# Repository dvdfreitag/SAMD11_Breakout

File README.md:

# SAMD11_Breakout
A breakout board for the Atmel ATSAMD11 microcontroller in QFN24

The ATSAMD11 is an extremely inexpensive USB-enabled microcontroller with an Arm Cortex-M0+ core running at a maximum 48MHz.

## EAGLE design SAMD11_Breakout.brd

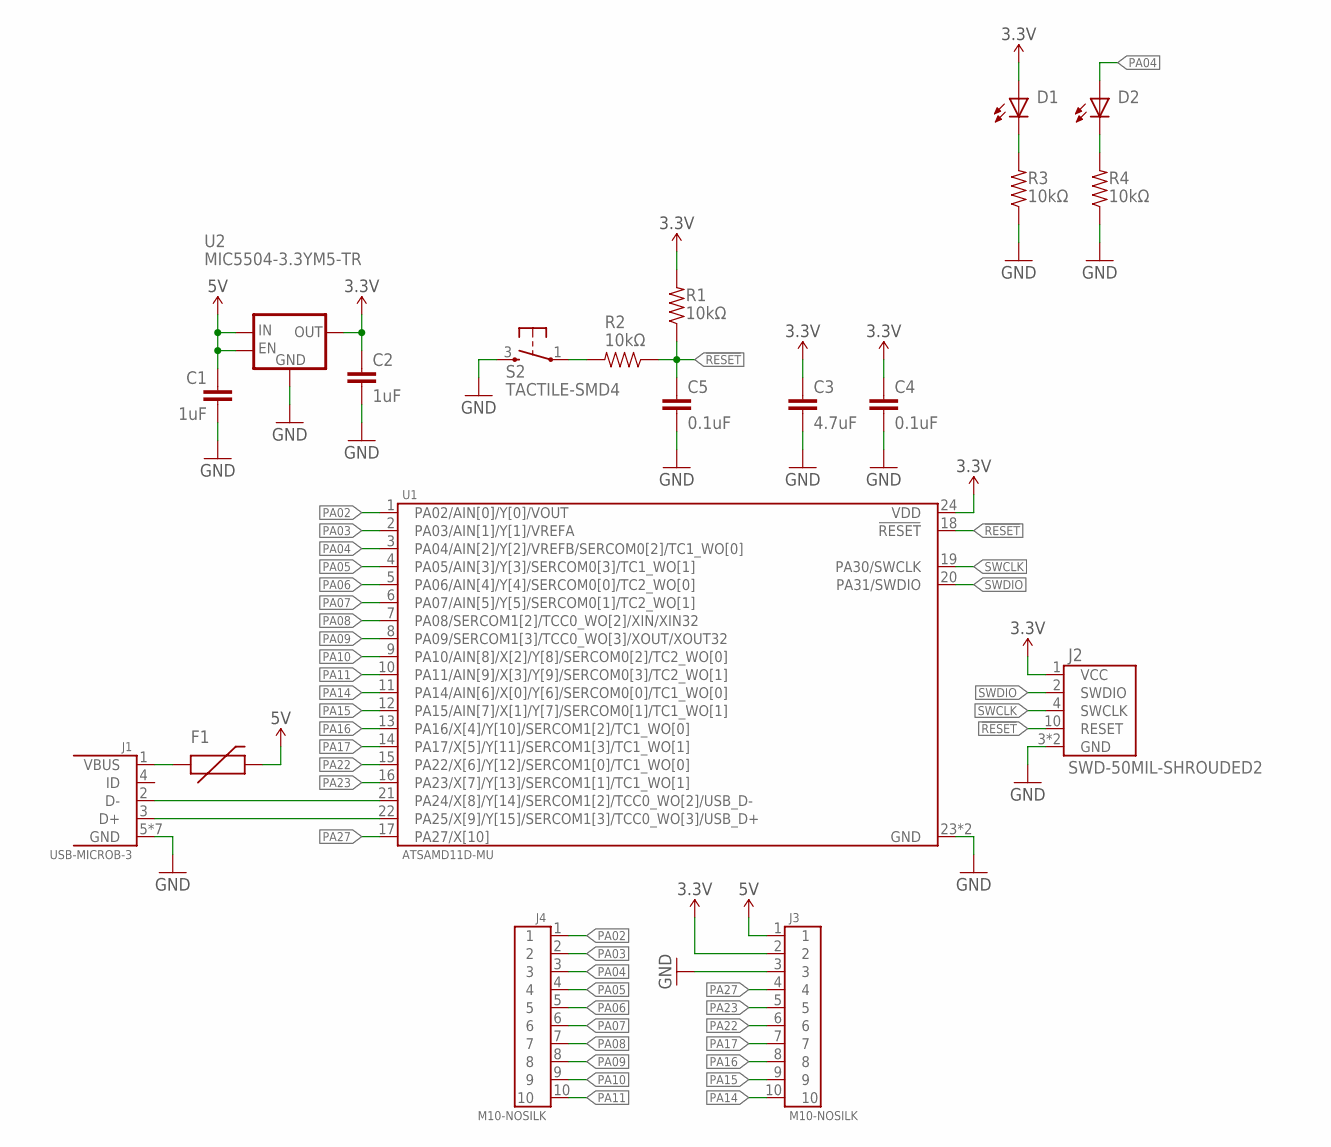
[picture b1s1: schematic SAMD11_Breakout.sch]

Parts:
C1, C2: 1uF; 0603-CAP
C3: 4.7uF; 0603-CAP
C4, C5: 0.1uF; 0603-CAP
D1, D2: LED-0603; 0603-LED
F1: PTC-1206; 1206-PTC
J1: USB-MICROB-3; 10118192-0001LF
J2: SWD-50MIL-SHROUDED2; M05X2-50MIL-SHROUD
J3, J4: M10-NOSILK; M10X1-NOSILK
R1, R2, R3, R4: 10kΩ; 0603-CAP
S2: TACTILE-SMD4; KMR741NG
U1: ATSAMD11D-MU; QFN-24
U2: MIC5504-3.3YM5-TR; SOT23-5

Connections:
3.3V: C2.1, C3.1, C4.1, D1.A, J2.1 (VCC), J3.2, R1.2, U1.24 (VDD), U2.5 (OUT)
5V: C1.1, F1.P$2 (2), J3.1, U2.1 (IN), U2.3 (EN)
!RESET: C5.1, J2.10 (RESET), R1.1, R2.1, U1.18 (!RESET)
D_N: J1.2 (D-), U1.21 (PA24/X[8]/Y[14]/SERCOM1[2]/TCC0_WO[2]/U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)
D_P: J1.3 (D+), U1.22 (PA25/X[9]/Y[15]/SERCOM1[3]/TCC0_WO[3]/U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)
GND: C1.2, C2.2, C3.2, C4.2, C5.2, J1.5 (GND), J1.P$6 (GND), J1.P$7 (GND), J1.P$8 (GND), J1.P$9 (GND), J1.P$10 (GND), J1.P$11 (GND), J2.3 (GND), J2.5 (GND), J3.3, R3.1, R4.1, S2.3, U1.23 (GND), U1.P$1 (GND), U2.2 (GND)
unnamed: R2.2, S2.1
unnamed: D2.C, R4.2
unnamed: D1.C, R3.2
unnamed: F1.P$1 (1), J1.1 (VBUS)
PA02: J4.1, U1.1 (PA02/AIN[0]/Y[0]/VOUT)
PA03: J4.2, U1.2 (PA03/AIN[1]/Y[1]/VREFA)
PA04: D2.A, J4.3, U1.3 (PA04/AIN[2]/Y[2]/VREFB/SERCOM0[2]/TC1_W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)
PA05: J4.4, U1.4 (PA05/AIN[3]/Y[3]/SERCOM0[3]/TC1_WO[1])
PA06: J4.5, U1.5 (PA06/AIN[4]/Y[4]/SERCOM0[0]/TC2_WO[0])
PA07: J4.6, U1.6 (PA07/AIN[5]/Y[5]/SERCOM0[1]/TC2_WO[1])
PA08: J4.7, U1.7 (PA08/SERCOM1[2]/TCC0_WO[2]/XIN/XIN32)
PA09: J4.8, U1.8 (PA09/SERCOM1[3]/TCC0_WO[3]/XOUT/XOUT32)
PA10: J4.9, U1.9 (PA10/AIN[8]/X[2]/Y[8]/SERCOM0[2]/TC2_WO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)
PA11: J4.10, U1.10 (PA11/AIN[9]/X[3]/Y[9]/SERCOM0[3]/TC2_WO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)
PA14: J3.10, U1.11 (PA14/AIN[6]/X[0]/Y[6]/SERCOM0[0]/TC1_WO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)
PA15: J3.9, U1.12 (PA15/AIN[7]/X[1]/Y[7]/SERCOM0[1]/TC1_WO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)
PA16: J3.8, U1.13 (PA16/X[4]/Y[10]/SERCOM1[2]/TC1_WO[0])
PA17: J3.7, U1.14 (PA17/X[5]/Y[11]/SERCOM1[3]/TC1_WO[1])
PA22: J3.6, U1.15 (PA22/X[6]/Y[12]/SERCOM1[0]/TC1_WO[0])
PA23: J3.5, U1.16 (PA23/X[7]/Y[13]/SERCOM1[1]/TC1_WO[1])
PA27: J3.4, U1.17 (PA27/X[10])
SWCLK: J2.4 (SWCLK), U1.19 (PA30/SWCLK)
SWDIO: J2.2 (SWDIO), U1.20 (PA31/SWDIO)

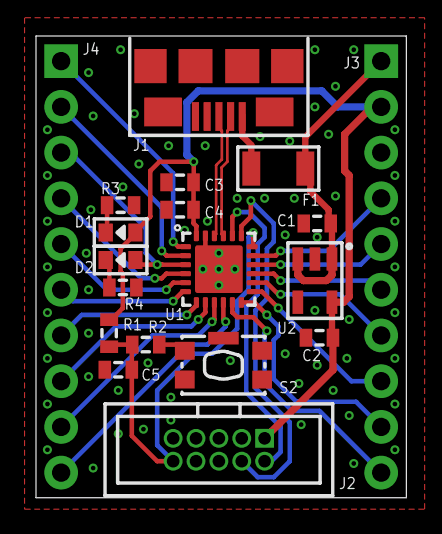
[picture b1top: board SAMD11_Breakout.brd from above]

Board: 2 copper layers, 20.6 x 25.7 mm, 19 parts (0 on the bottom side), 29 nets.

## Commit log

2018-04-30 Create LICENSE
2018-04-30 Add schematic pdf
